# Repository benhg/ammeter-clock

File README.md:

# KN6UBF analog meter clock

An Arduino Uno shield driving a 0–15 V hour meter and 0–100 µA minute meter.
The built, calibrated clock uses Rev F4 (root KiCad project). **Rev 2** adds a
seconds meter and rotates J5 for easier external-button wiring. It lives separately
under [hardware/rev2](hardware/rev2/README.md), with its own fabrication archive.
Rev 2 passes ERC, DRC, netlist, Uno geometry and interface simulations; its new
mechanicals and seconds channel still need a physical prototype.

[Clock Setup](https://benhg.github.io/ammeter-clock/) configures time, timezone,
Wi-Fi and calibration over USB. [Download a desktop app](https://github.com/benhg/ammeter-clock/releases)
for Windows, macOS or Linux to flash firmware as well. The native desktop app uses Qt Widgets and includes Python and Arduino CLI;
first flash downloads board support. Firmware installation is separate from connecting.

Firmware 0.3.0 adds a guided calibration wizard: mechanical zero, held 12:30
reference, lower/raise adjustments, optional seconds, arbitrary test values and a
sweep before saving. Existing firmware settings migrate with hour/minute calibration
and Wi-Fi retained; seconds defaults off. The running clock is not flashed automatically.

Both onboard and external HOUR/MINUTE buttons work on R3 and R4 WiFi. Holding
both for three seconds resumes Wi-Fi/NTP on R4; individual time adjustments pause
NTP until that gesture, USB Resume NTP or restart. An RTC is optional and not read
by this firmware; R3 must be set again after power loss. R4 can resync over Wi-Fi.

- [Firmware, serial protocol and limitations](firmware/README.md)
- [Setup app instructions](tools/clock_setup/README.md)
- [Rev 2 design, checks and fabrication files](hardware/rev2/README.md)

The shield uses a customer-installed Pololu U3V16F15 15 V module in U4's socket.
Meter outputs default disabled on a new installation. The minute/second drivers
have 56 kΩ series resistors and require microamp movements, not milliamp meters.
Manufacturer macro-model simulations impose the 15 V supply; they do not simulate
the Pololu converter or the DAC's EEPROM power-on state.

Desktop app / firmware 0.4.0 adds R4 Wi-Fi network search, native password visibility
control and a dedicated USB connection panel. Customer macOS releases now require
Developer ID signing and Apple notarization.

Version 0.5.0 adds a smooth one-second app clock, disconnect-and-search Wi-Fi,
searchable IANA zones with saved daylight-saving transitions, editable custom
offsets, and 5–600 second meter sweeps. Resume NTP is disabled while already active.

Before shipping assembled clocks, follow the [pre-shipment test checklist](docs/PRE-SHIP-TEST.md), including the separate R4 Wi-Fi firmware update and cold-start NTP verification.

Desktop app 0.6.0 adds the R4 Wi-Fi module updater: install qualified connectivity
firmware, follow the power-cycle prompt, and restore/verify clock firmware from the
same app. Recovery survives closing and reopening the app.

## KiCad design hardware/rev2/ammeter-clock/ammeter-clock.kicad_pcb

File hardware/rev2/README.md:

# Rev 2 — seconds meter and accessible minute button terminal

This is an isolated successor to the built Rev F4 two-meter shield. Open
`ammeter-clock/ammeter-clock.kicad_pro` here in KiCad 8. The root project is the
Rev F4 baseline and is not replaced by Rev 2.

- R10 (56 kΩ, 1%) and J10 (two-position 5 mm screw terminal) duplicate R3/J3.
  MCP4728 B / pin 7 drives R10 → J10 pin 1 (+); pin 2 is GND.
- Hours remain on DAC D / pin 9; minutes remain on C / pin 8. A / pin 6 is unused.
  The old schematic's reversed channel *names* were corrected to match these pins.
- J5 rotates 180° around its body center, with wire entry toward the board center,
  away from the bottom power header. Its signal/GND pad assignments follow the
  rotated connector. Route external button wiring through the open center corridor.
- Same Uno outline, mounting holes, stackable headers, R3/R4 WiFi signals and
  underside/antenna exclusions. Pololu module and all other electrical values stay.
- 28 assembled components: 6 SMT, 22 through-hole; customer installs the Pololu
  module in U4's assembler-fitted socket. Seconds needs another **0–100 µA** needle
  movement. Firmware 0.3.0 enables that channel through the calibration wizard.

`fabrication/ammeter-clock-rev2-fabrication.zip` contains the Gerbers, full BOM/CPL,
manifest and check summaries. The BOM reuses F4 catalogue parts; current stock
has not been rechecked. This is a prototype package, not a bench-qualified release.

Validation: zero ERC/DRC violations, zero unconnected pads; all 32 component
references including four mounting holes match between schematic and board.
Both Uno header geometries and signal assignments pass. 205 ngspice analyses,
including 18 simultaneous minute/second load corners and seconds rollover/short,
plus six engineering input-clamp cases pass. Ideal DAC sources and imposed boost
rails do not establish converter startup, crosstalk or needle dynamics. New terminal
access, physical stack clearances and seconds response still need a built Rev 2.

To rerun from repository root (KiCad 8 Python is required for PCB scripts):

```sh
export AMMETER_PROJECT_DIR="$PWD/hardware/rev2"
kicad-cli sch export netlist --format kicadxml -o hardware/rev2/reports/netlist.xml hardware/rev2/ammeter-clock/ammeter-clock.kicad_sch
python scripts/check_hardware.py
python scripts/check_shield.py
python scripts/check_r4_wifi.py
python simulations/run_simulations.py
python simulations/check_input_protection.py
python scripts/export_rev2.py
```

Use the Python bundled with KiCad where `pcbnew` is imported. Set PATH to include
`ngspice`. Raw simulation traces are regenerated locally; summary JSON/CSVs and
source decks/models are retained. `build_rev2.py` is the historical one-time fork
from the root F4 snapshot; it refuses to overwrite an existing Rev 2 project.
Subsequent layout edits should be made in KiCad, then checked and exported again.

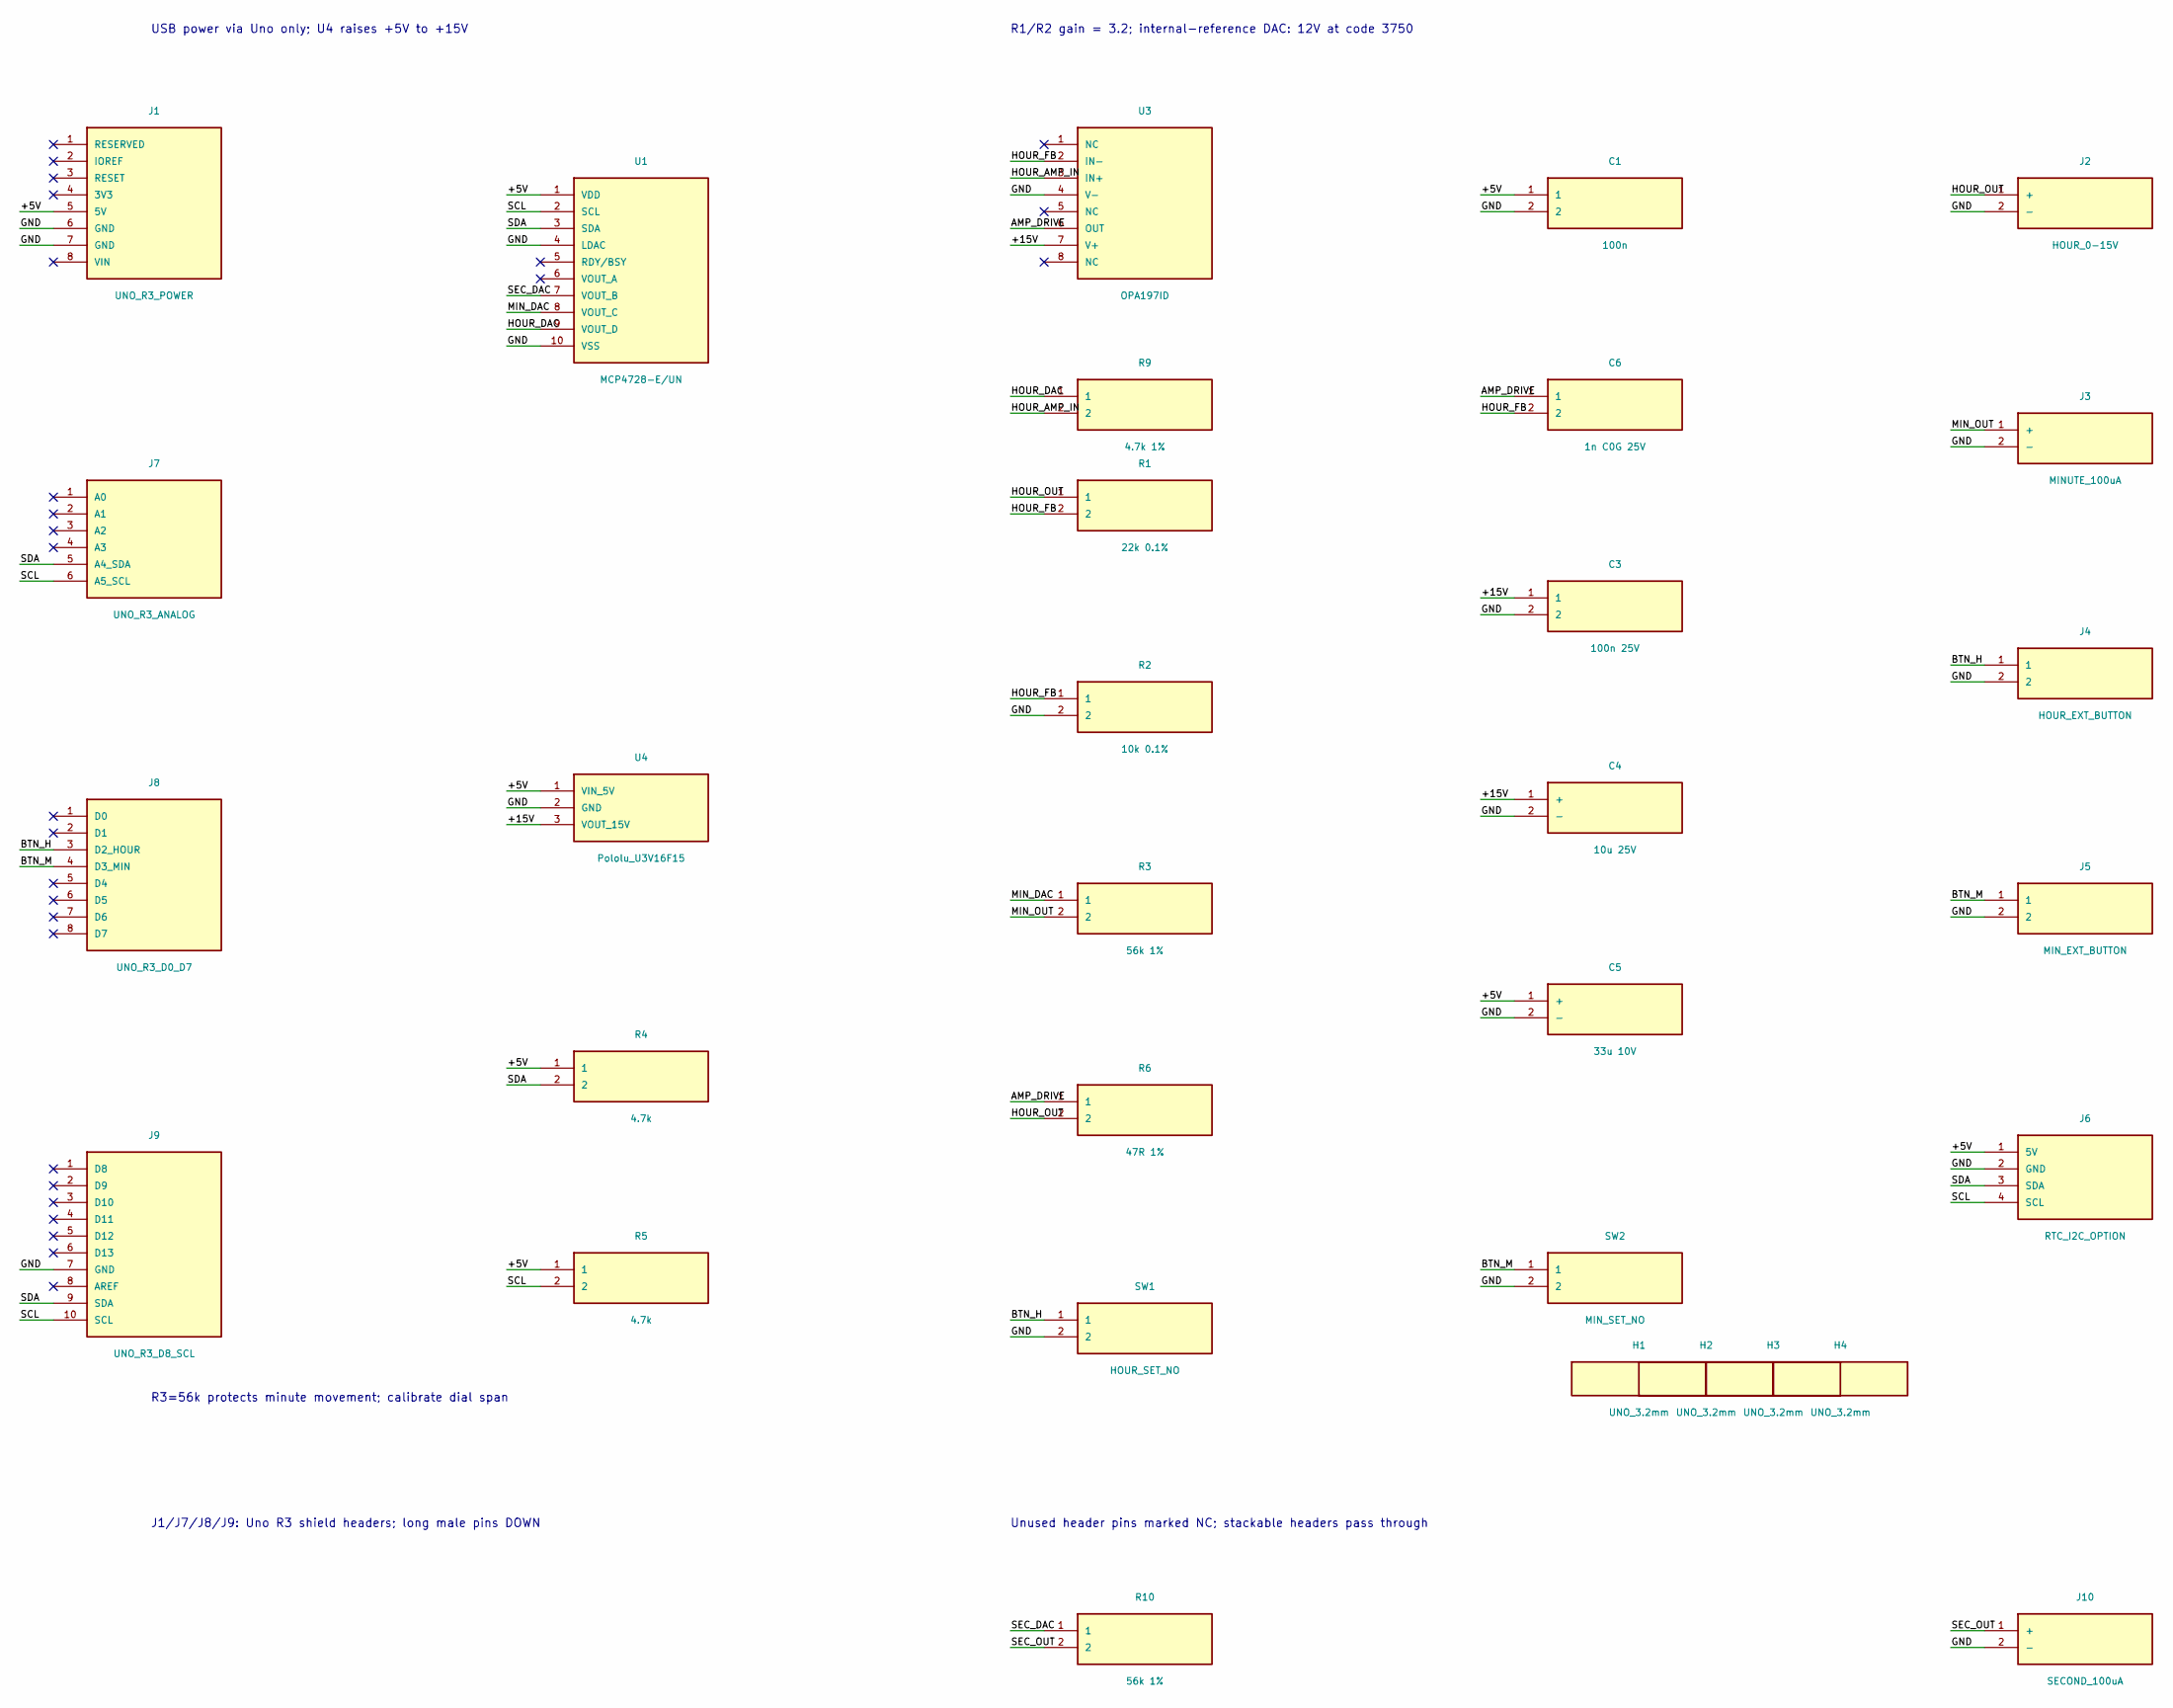
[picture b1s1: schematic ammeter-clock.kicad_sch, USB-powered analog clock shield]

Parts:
C1: 100n; FH_CT4_0805_P5.08mm
C3: 100n 25V; FH_CT4_0805_P5.08mm
C4: 10u 25V; CP_Radial_D5.0mm_P2.00mm
C5: 33u 10V; CP_Radial_D6.3mm_P2.50mm
C6: 1n C0G 25V; C_0805_2012Metric
H1, H2, H3, H4: UNO_3.2mm; Uno_MountHole_3.2mm
J1: UNO_R3_POWER; Uno_R3_Stackable_1x08
J2: HOUR_0-15V; JILN_JL301_2P_P5.00mm
J3: MINUTE_100uA; JILN_JL301_2P_P5.00mm
J4: HOUR_EXT_BUTTON; JILN_JL301_2P_P5.00mm
J5: MIN_EXT_BUTTON; JILN_JL301_2P_P5.00mm
J6: RTC_I2C_OPTION; PinHeader_1x04_P2.54mm_Vertical
J7: UNO_R3_ANALOG; Uno_R3_Stackable_1x06
J8: UNO_R3_D0_D7; Uno_R3_Stackable_1x08
J9: UNO_R3_D8_SCL; Uno_R3_Stackable_1x10
J10: SECOND_100uA; JILN_JL301_2P_P5.00mm
R1: 22k 0.1%; R_0805_2012Metric
R2: 10k 0.1%; R_0805_2012Metric
R3, R10: 56k 1%; R_Axial_DIN0207_L6.3mm_D2.5mm_P7.62mm_Horizontal
R4, R5: 4.7k; R_Axial_DIN0207_L6.3mm_D2.5mm_P7.62mm_Horizontal
R6: 47R 1%; R_Axial_DIN0207_L6.3mm_D2.5mm_P7.62mm_Horizontal
R9: 4.7k 1%; R_0805_2012Metric
SW1: HOUR_SET_NO; SW_PUSH_6mm
SW2: MIN_SET_NO; SW_PUSH_6mm
U1: MCP4728-E/UN; MSOP-10_3x3mm_P0.5mm
U3: OPA197ID; SOIC-8_3.9x4.9mm_P1.27mm
U4: Pololu_U3V16F15; Pololu_U3V16F15_Socket

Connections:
/+5V: C1.1, C5.1 (+), J1.5 (5V), J6.1 (5V), R4.1, R5.1, U1.1 (VDD), U4.1 (VIN_5V)
/+15V: C3.1, C4.1 (+), U3.7 (V+), U4.3 (VOUT_15V)
/AMP_DRIVE: C6.1, R6.1, U3.6 (OUT)
/BTN_H: J4.1, J8.3 (D2_HOUR), SW1.1
/BTN_M: J5.1, J8.4 (D3_MIN), SW2.1
/GND: C1.2, C3.2, C4.2 (-), C5.2 (-), J1.6 (GND), J1.7 (GND), J2.2 (-), J3.2 (-), J4.2, J5.2, J6.2 (GND), J9.7 (GND), J10.2 (-), R2.2, SW1.2, SW2.2, U1.4 (LDAC), U1.10 (VSS), U3.4 (V-), U4.2 (GND)
/HOUR_AMP_IN: R9.2, U3.3 (IN+)
/HOUR_DAC: R9.1, U1.9 (VOUT_D)
/HOUR_FB: C6.2, R1.2, R2.1, U3.2 (IN-)
/HOUR_OUT: J2.1 (+), R1.1, R6.2
/MIN_DAC: R3.1, U1.8 (VOUT_C)
/MIN_OUT: J3.1 (+), R3.2
/SCL: J6.4 (SCL), J7.6 (A5_SCL), J9.10 (SCL), R5.2, U1.2 (SCL)
/SDA: J6.3 (SDA), J7.5 (A4_SDA), J9.9 (SDA), R4.2, U1.3 (SDA)
/SEC_DAC: R10.1, U1.7 (VOUT_B)
/SEC_OUT: J10.1 (+), R10.2

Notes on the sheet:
USB power via Uno only; U4 raises +5V to +15V
R1/R2 gain = 3.2; internal-reference DAC: 12V at code 3750
R3=56k protects minute movement; calibrate dial span
J1/J7/J8/J9: Uno R3 shield headers; long male pins DOWN
Unused header pins marked NC; stackable headers pass through

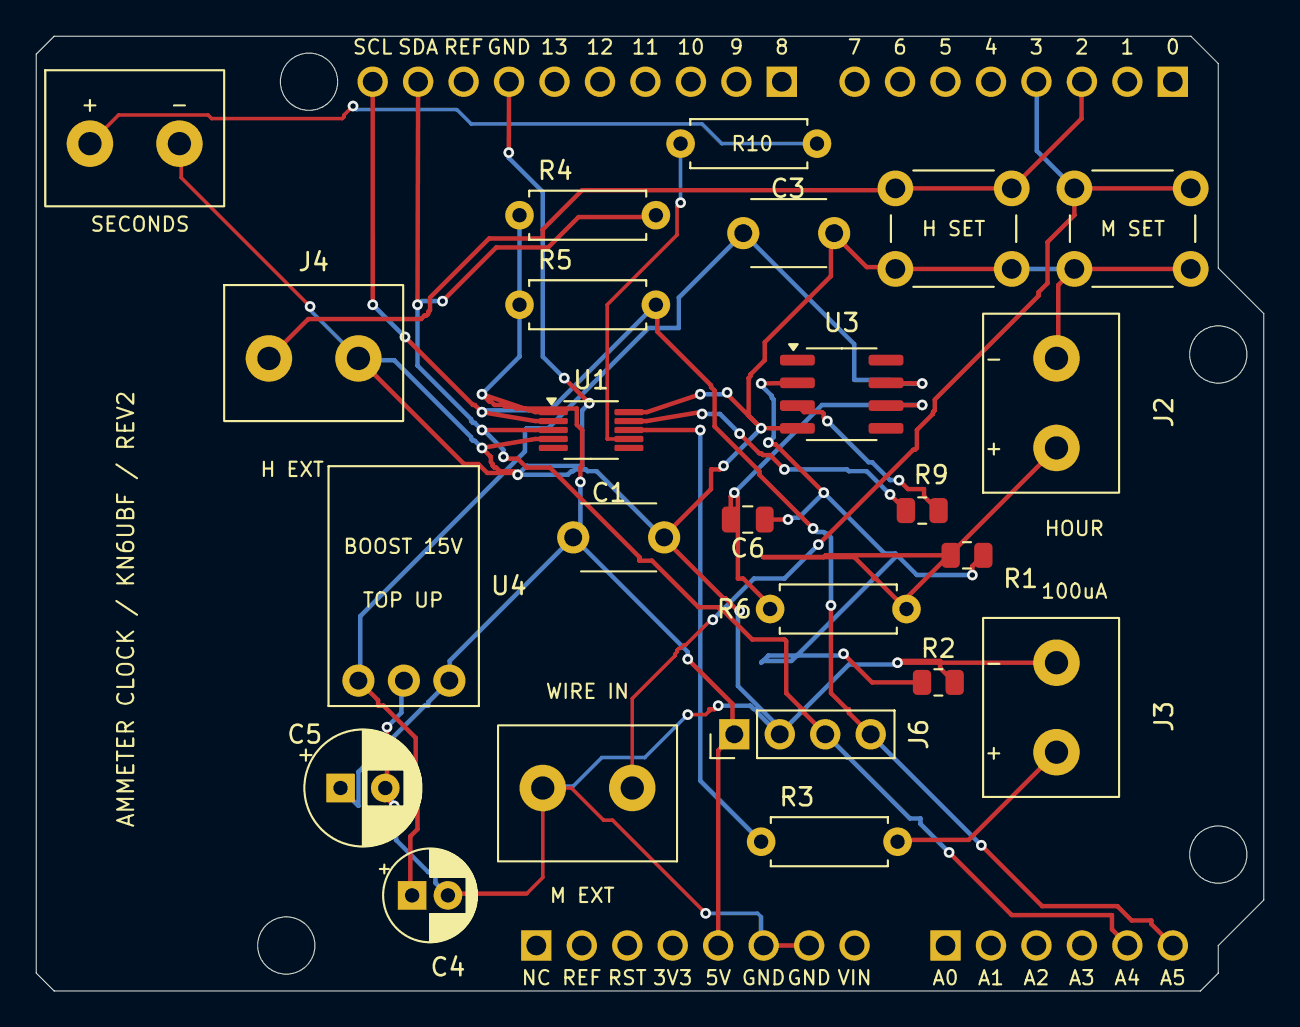
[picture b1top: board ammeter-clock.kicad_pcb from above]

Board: 2 copper layers, 68.6 x 53.3 mm, 32 parts (0 on the bottom side), 16 nets.

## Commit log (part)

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2024-12-10 edits
